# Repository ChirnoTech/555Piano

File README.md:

555Piano
==========
Small sized 555 timer based piano. All parts are smd type.

[Youtube presentation][1]

[1]: https://youtu.be/Ph5YViHxxoE

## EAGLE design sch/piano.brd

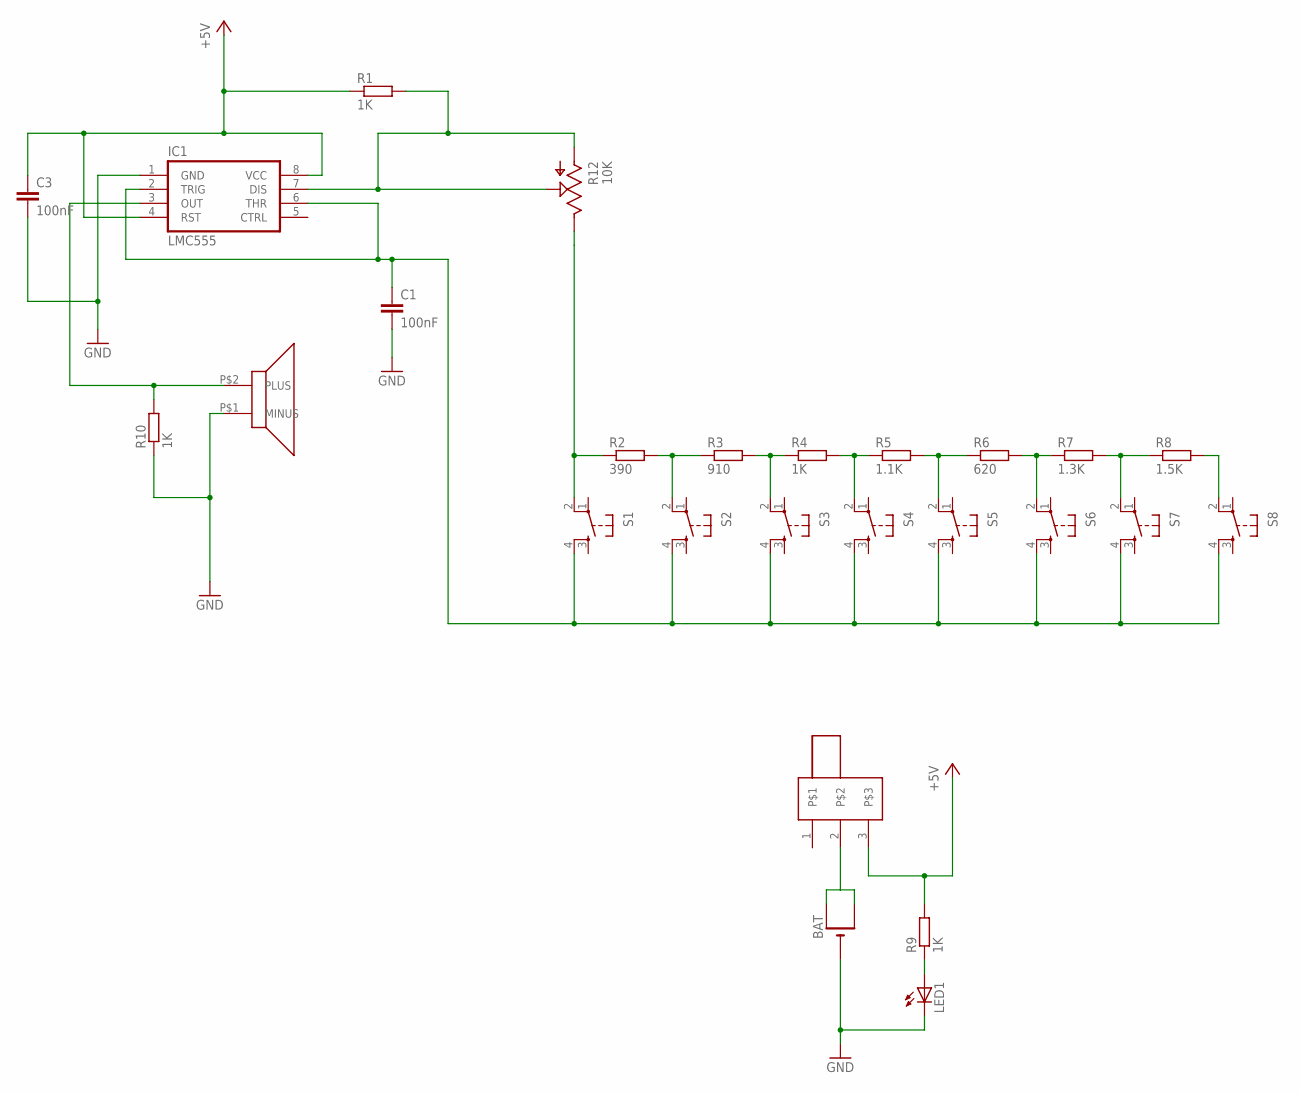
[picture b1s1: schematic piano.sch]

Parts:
BAT: CR1220SMT; CR1220-SMD
C1, C3: 100nF; C1206
IC1: LMC555; SOIC-8
LED1: LED1206; LED-1206
R1, R4, R9, R10: 1K; R1206
R2: 390; R1206
R3: 910; R1206
R5: 1.1K; R1206
R6: 620; R1206
R7: 1.3K; R1206
R8: 1.5K; R1206
R12: 10K; PVZ3A
S1, S2, S3, S4, S5, S6, S7, S8: TAC_SWITCHSMD; TACTILE_SWITCH_SMD
U$1: SMD-100030H-05052T; SMD-100030H
U$2: SK12D07VG3; SWITCH3

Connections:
+5V: C3.1, IC1.4 (RST), IC1.8 (VCC), R1.1, R9.2, U$2.3
GND: BAT.-, C1.2, C3.2, IC1.1 (GND), LED1.C, R10.1, U$1.P$1 (MINUS)
unnamed: R2.1, R12.P$3, S1.2
unnamed: R2.2, R3.1, S2.2
unnamed: R3.2, R4.1, S3.2
unnamed: R4.2, R5.1, S4.2
unnamed: IC1.7 (DIS), R1.2, R12.P$1, R12.P$2
unnamed: R5.2, R6.1, S5.2
unnamed: IC1.3 (OUT), R10.2, U$1.P$2 (PLUS)
unnamed: C1.1, IC1.2 (TRIG), IC1.6 (THR), S1.4, S2.4, S3.4, S4.4, S5.4, S6.4, S7.4, S8.4
unnamed: R6.2, R7.1, S6.2
unnamed: R7.2, R8.1, S7.2
unnamed: R8.2, S8.2
unnamed: BAT.+$1 (+), BAT.+$2 (+1), U$2.2
unnamed: LED1.A, R9.1

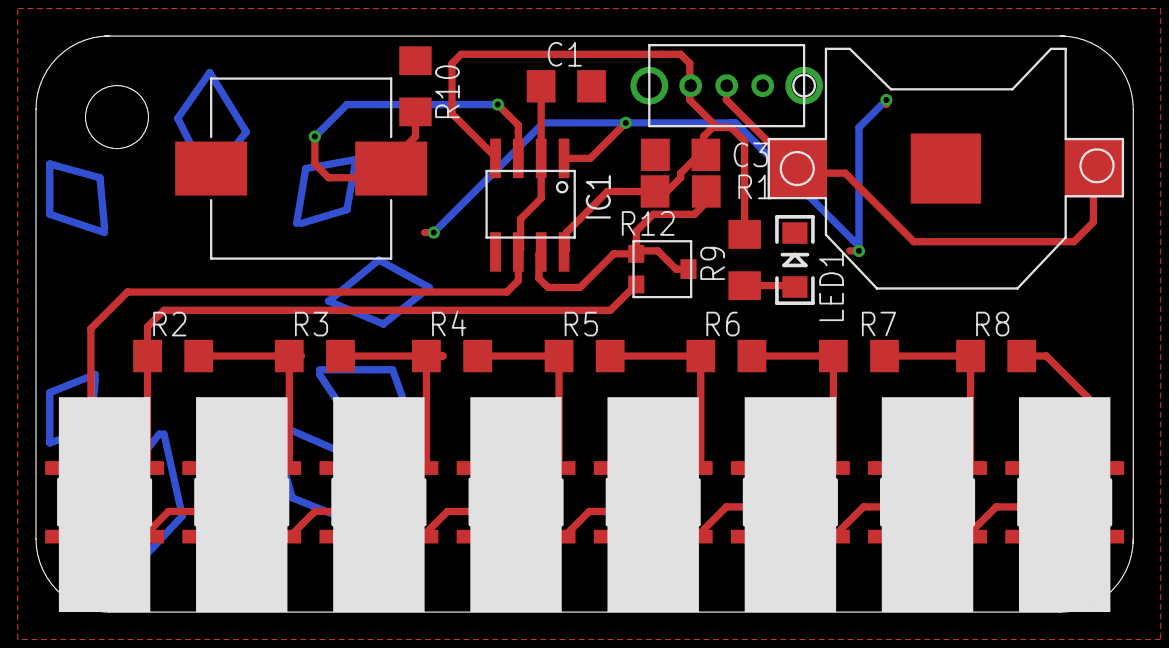
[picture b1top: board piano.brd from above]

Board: 2 copper layers, 61.0 x 32.0 mm, 26 parts (0 on the bottom side), 15 nets.

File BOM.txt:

Partlist exported from sch/piano.sch at 13.03.2017 22:42:54

Assembly variant: 

Qty Value              Device             Parts                         
1                      CR1220SMT          BAT                           
1                      LED1206            LED1                          
8                      TAC_SWITCHSMD      S1, S2, S3, S4, S5, S6, S7, S8
1   1.1K               R-EU_R1206         R5                            
1   1.3K               R-EU_R1206         R7                            
1   1.5K               R-EU_R1206         R8                            
4   1K                 R-EU_R1206         R1, R4, R9, R10               
1   10K                PVZ3A              R12                           
2   100nF              C-EUC1206          C1, C3                        
1   390                R-EU_R1206         R2                            
1   620                R-EU_R1206         R6                            
1   910                R-EU_R1206         R3                            
1   LMC555             IC_555-SOIC8       IC1                           
1   SK12D07VG3         SWITCH3            SWITCH                           
1   SMD-100030H-05052T SMD-100030H-05052T BUZZER

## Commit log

2017-03-13 Upload schematic, bom and some info

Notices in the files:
parts and their libraries:
SparkFun-Electromechanical: Licensing: CC v3.0 Share-Alike You are welcome to use this library for commercial purposes.
